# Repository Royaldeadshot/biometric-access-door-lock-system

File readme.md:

# ESP32 Based Biometric Access Door Lock (Tailored for GYM)

## Motivation
I used to go my GYM and used to see this biometric access door lock, and one day it struck me, I can make one too, with some extra features. So here i'm building this.

## Features
1. **Fingerprint** Based Recognition.
2. **Exit** by Pressing a Button inside.
3. **Cool LED ring** around the Fingerprint sensor for Visual Feedback, which also shows cool animations while idle.
4. **Buzzer** for Audible Feedback.
5. **Real Time member** list fetching from Website's Database. (No extra hardware like a laptop required for its working, just a wifi connection and it works like a charm.)
6. **Easy Integration** with any custom website.
7. A Fail Secure Solenoid Door Lock, it keeps locked when electricity is gone.

## Parts List

| Name | Qty | Link | $ Price |
| --- | --- | --- | --- |
| ESP32                            | 1 | https://robocraze.com/products/esp32-development-board?_pos=1&_psq=esp&_psid=ffe363e30&_ss=e                                                                     | 4.17 |
| R307S Fingerprint Scanner Module | 1 | https://robu.in/product/r307-optical-fingerprint-reader-module-sensor/                                                                                           | 9.52 |
| Solenoid Door Lock               | 1 | https://robocraze.com/products/12v-dc-lock-electric-solenoid-assembly?_pos=1&_sid=4b8eba6e6&_ss=r                                                                | 3.85 |
| 12V Power supply                 | 1 | https://robocraze.com/products/12-volt-2-amp-power-adapter-ac-to-dc?_pos=1&_psq=12v&_psid=6336dae56&_ss=e                                                        | 1.88 |
| 12V Relay                        | 1 | https://robocraze.com/products/12v-2-channel-relay-module-with-optocoupler-isolation?_pos=6&_sid=333247d21&_ss=r                                                 | 0.93 |
| 12V to 5V Buck converter         | 1 | https://robocraze.com/products/lm2596-dc-dc-buck-module?_pos=1&_psq=LM2596+DC-DC+Buck+Converter+Adjustable+Step+Down+Power+Supply+Module&_psid=99fdbbb4d&_ss=e   | 0.5 |
| Buzzer                           | 1 | https://robocraze.com/products/3-volts-buzzer-small?_pos=1&_sid=47bbfcefe&_ss=r                                                                                  | 0.15 |
| Diode                            | 1 | https://robocraze.com/products/1n4007-diode-pack-of-10?_pos=1&_sid=7c56ba663&_ss=r                                                                               | 0.16 |
| Switch                           | 1 | any kind of push switch works                                                                                                                                    | 0 |
| LED (sk6812 mini e)              | 8 | I just have them, i don't have a link of those                                                                                                                   | 0 |
| 3d Printed Enclosure             | 1 | Source by Hackclub Printing  Legion                                                                                                                              | 5 |
| Diffuser sheet                   | 1 | find something which can diffuse light well enough                                                                                                               | 0 |
| Jumper wires                     | - | https://robocraze.com/products/jumper-wire-set-m2m-m2f-f2f-40-pcs-each                                                                                           | 1.45 |
| M3 Heatset inserts               | 4 | -                                                                                                                                                                | 0 |
| M3 Screws                        | 4 | -                                                                                                                                                                | 0 |
|                                  |   | TOTAL                                                                                                                                                            | 27.61 |
## Images
### Wiring

### 3D Model

## FInished Build Image

## Code
Code avaialble In the Code folder of this repository. Flash the code using arduino ide, and also install theese libraries Adafruit Fingerprint, FastLED, Firebase ESP32 Client.

## Working Flow

### 1. Access Attempt → Member Scans Finger
1. Member places finger on the R307S fingerprint scanner.
2. The R307S captures the scan and checks it against the fingerprint templates stored on the sensor itself, retrieving a matched fingerprint ID if one exists.
3. The ESP32 takes that fingerprint ID and queries the gym management website's database to check whether a member record is linked to it.

Case A — Member found, membership active

LED ring blinks green
* Buzzer beeps once
* Relay activates, retracting the solenoid lock for 2-3 seconds (exact duration to be finalized after physical testing)
* Door opens, lock releases automatically once the retract window ends

Case B — Member found, membership expired

* LED ring blinks red
* Buzzer beeps rapidly, 3 times
* Lock stays engaged, door does not open

Case C — Fingerprint not recognized (no matching record)

* LED ring turns orange
* Buzzer stays silent
* Lock stays engaged door does not open

### 2. Exit → Push Button
* Member presses the exit button on the inside of the door.
* No fingerprint check is required, this triggers the relay directly, retracting the lock and opening the door.
* This ensures free exit at all times, independent of the membership check or fingerprint recognition.

### 3. New Member Enrollment
1. Gym owner clicks "Register" on the gym management website and fills in the new member's details.
2. The website sends an enrollment request to the ESP32.
3. The ESP32 switches the R307S sensor into enrollment mode.
4. During this process, the LED ring displays a circular loading animation in yellow, giving visual feedback that enrollment is in progress.
5. The new member places their finger on the scanner, the sensor captures and stores the fingerprint template internally, generating a new fingerprint ID.
6. Once the scan completes successfully, the LED animation turn purple for 5 seconds and then goes to idle, (signaling completion).
7. The ESP32 sends the newly generated fingerprint ID back to the website, which stores it against that member's record in the database completing the link between "fingerprint" and "member."

## Website
* The website is hosted and accesible on this url- https://fitnessbox.vercel.app
* Here is the website's Repo link- https://github.com/Royaldeadshot/gym-management
* Just Copy the repo and host it and connect firebase and add email/password auth to acces the site.
* Currently the website is not integrated yet, once i get the parts all joined up then I will connect the two, the website and the biometric door lock system.

## Assembly Instruction
Insert the Fingerprint Sensor into the front plate from the front by sliding it in, and apply hot glue gun to fix it there, and using soldering iron, insert the heatset insert into the front plate and then place the led on a circular cardboard and place them there with superglue aand wire them up and then place them from the behind matching with holes provided in the circular ring. now keep the front and back open of the enclosure and place the esp32 and the relay and buck converter, hot glue them to fix them in place, and do the wiring as mentioned in the wiring diagram, and then close the frontplate and screw it in now run the 12v power wires, exit switch wire, solenoid door lock wires, from the hole at the back and wire them up with their respective part. for diffusion, i will place a tanslucent acrylic or plastic sheet by cutting it in circular shape and insert it in, and fill the groove with hot glue gun using the white glue stick which is nearly opaque. And then connect the esp32 with pc to flash the code, and then close up the back panel, it will just fir in right there by pushing it in.

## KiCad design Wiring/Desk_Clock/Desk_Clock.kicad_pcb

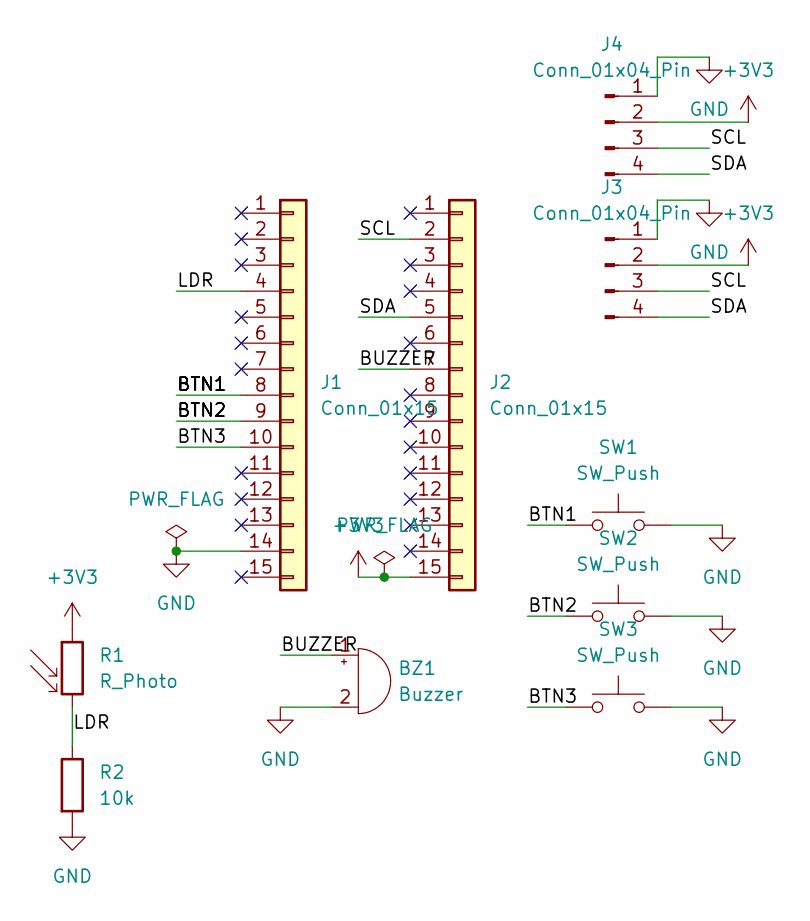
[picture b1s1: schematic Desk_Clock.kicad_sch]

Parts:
BZ1: Buzzer; Buzzer_12x9.5RM7.6
J1, J2: Conn_01x15; PinSocket_1x15_P2.54mm_Vertical
J3, J4: Conn_01x04_Pin; PinSocket_1x04_P2.54mm_Vertical
R1: R_Photo; R_LDR_5.1x4.3mm_P3.4mm_Vertical
R2: 10k; R_Axial_DIN0207_L6.3mm_D2.5mm_P10.16mm_Horizontal
SW1, SW2, SW3: SW_Push; SW_PUSH_6mm

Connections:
+3V3: J2.15, J3.2, J4.2, R1.1
/BTN1: J1.8, SW1.1
/BTN2: J1.9, SW2.1
/BTN3: J1.10, SW3.1
/BUZZER: BZ1.1 (+), J2.7
/LDR: J1.4, R1.2, R2.1
/SCL: J2.2, J3.3, J4.3
/SDA: J2.5, J3.4, J4.4
GND: BZ1.2 (-), J1.14, J3.1, J4.1, R2.2, SW1.2, SW2.2, SW3.2

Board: 2 copper layers, 10 parts (0 on the bottom side), 9 nets, no tracks yet.
